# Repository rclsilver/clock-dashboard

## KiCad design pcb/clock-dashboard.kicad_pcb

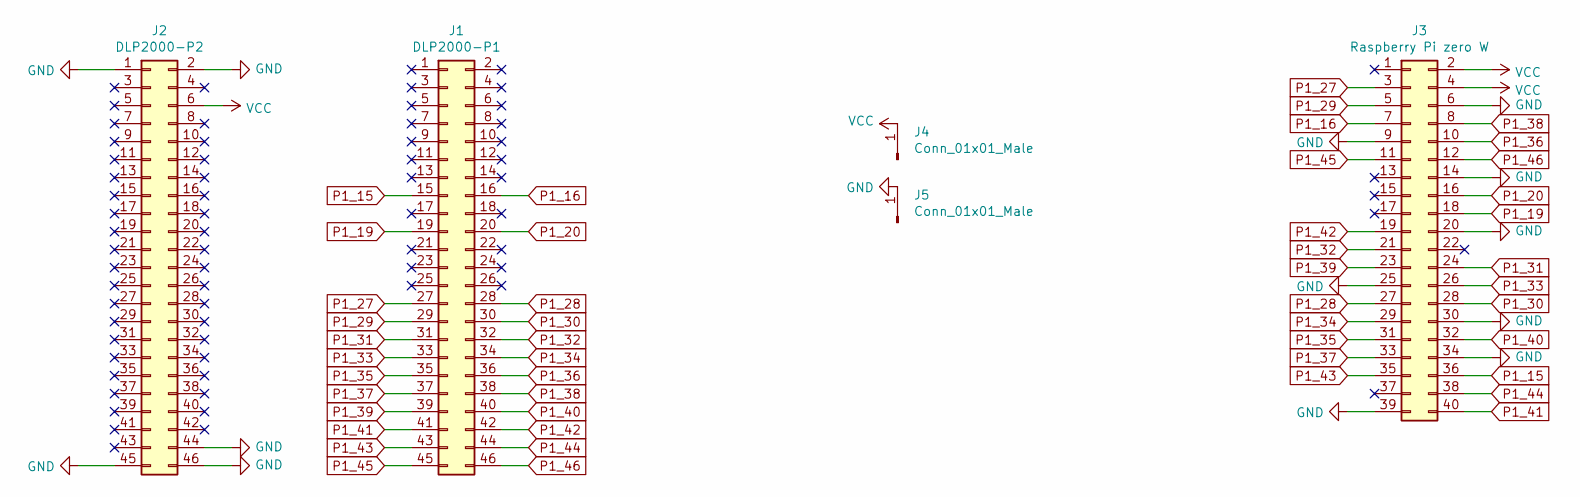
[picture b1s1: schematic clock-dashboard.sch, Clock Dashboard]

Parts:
J1: DLP2000-P1; PinHeader_2x23_P2.54mm_Vertical
J2: DLP2000-P2; PinHeader_2x23_P2.54mm_Vertical
J3: Raspberry Pi zero W; PinHeader_2x20_P2.54mm_Vertical
J4, J5: Conn_01x01_Male; TestPoint_Pad_2.0x2.0mm

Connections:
GND: J2.1, J2.2, J2.44, J2.45, J2.46, J3.6, J3.9, J3.14, J3.20, J3.25, J3.30, J3.34, J3.39, J5.1
P1_15: J1.15, J3.36
P1_16: J1.16, J3.7
P1_19: J1.19, J3.18
P1_20: J1.20, J3.16
P1_27: J1.27, J3.3
P1_28: J1.28, J3.27
P1_29: J1.29, J3.5
P1_30: J1.30, J3.28
P1_31: J1.31, J3.24
P1_32: J1.32, J3.21
P1_33: J1.33, J3.26
P1_34: J1.34, J3.29
P1_35: J1.35, J3.31
P1_36: J1.36, J3.10
P1_37: J1.37, J3.33
P1_38: J1.38, J3.8
P1_39: J1.39, J3.23
P1_40: J1.40, J3.32
P1_41: J1.41, J3.40
P1_42: J1.42, J3.19
P1_43: J1.43, J3.35
P1_44: J1.44, J3.38
P1_45: J1.45, J3.11
P1_46: J1.46, J3.12
VCC: J2.6, J3.2, J3.4, J4.1

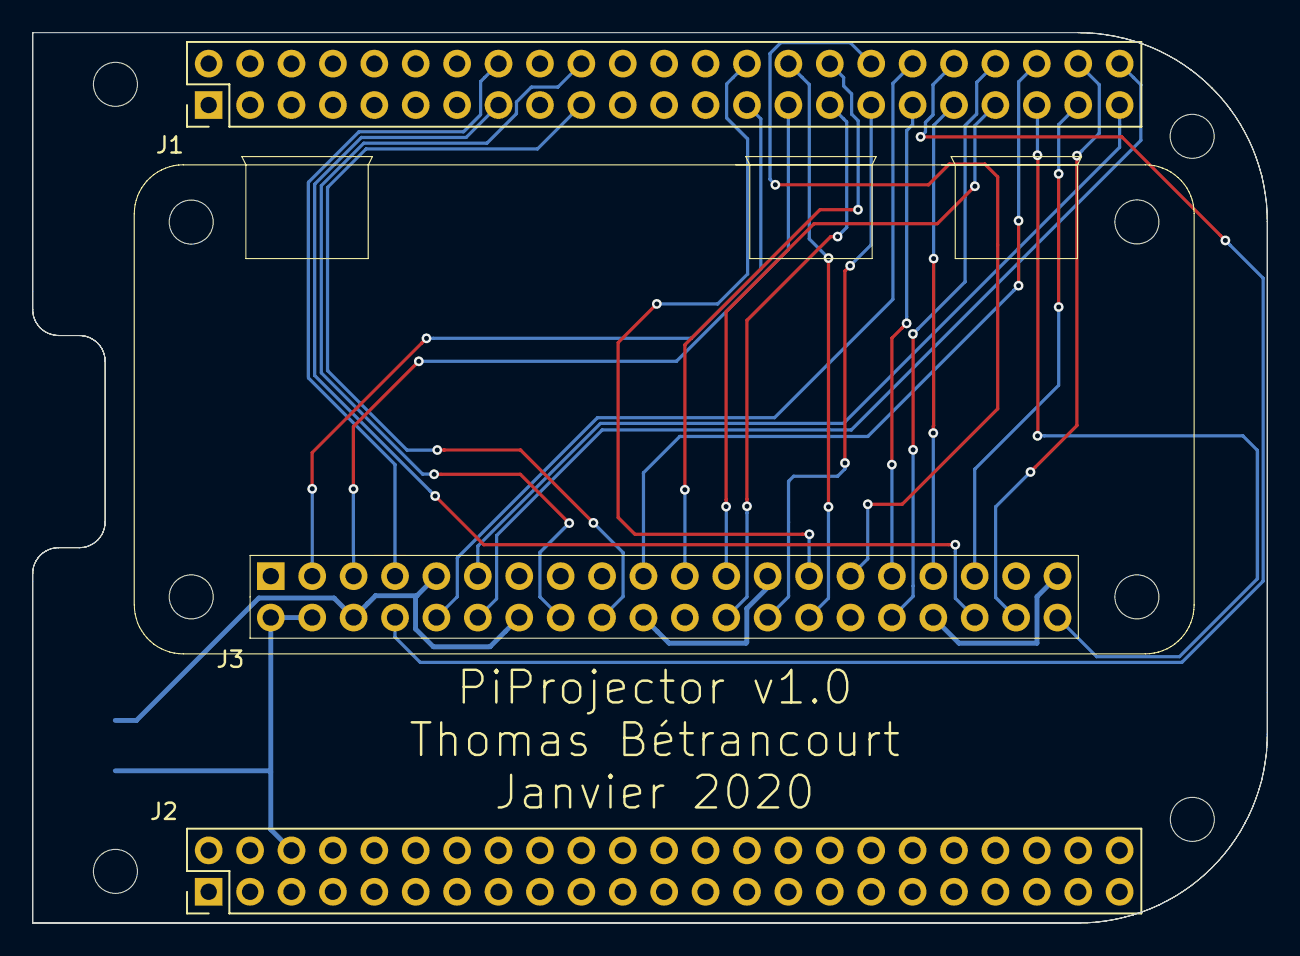
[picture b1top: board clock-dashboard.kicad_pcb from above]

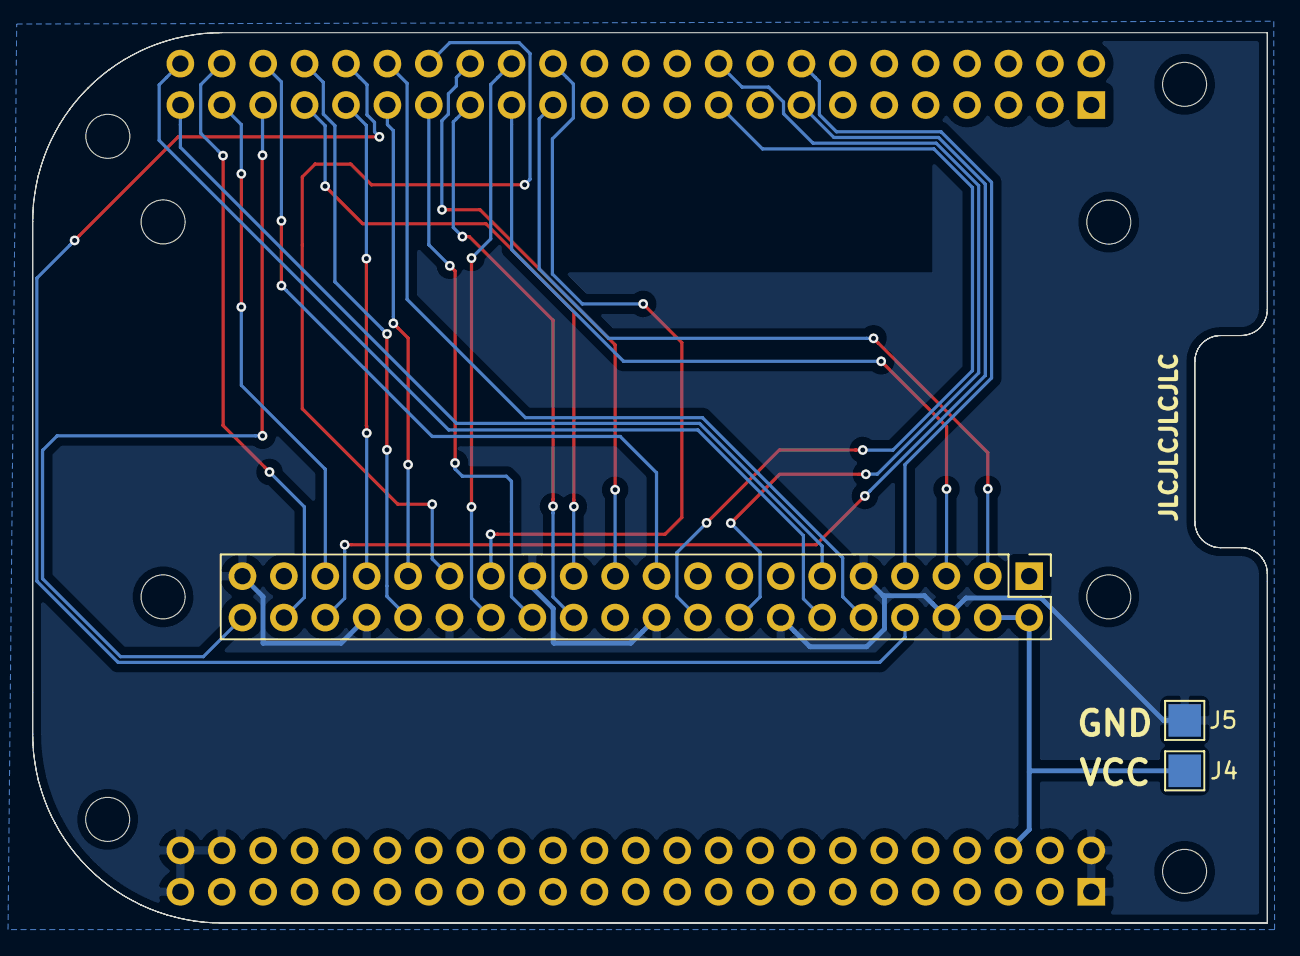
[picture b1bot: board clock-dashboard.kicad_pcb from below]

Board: 2 copper layers, 75.7 x 54.6 mm, 5 parts (3 on the bottom side), 26 nets.

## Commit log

2020-01-04 [web] Initial version
2020-01-04 [pcb] First version - Order Y2-2638412A
2020-01-04 [web] Add weather forecast
